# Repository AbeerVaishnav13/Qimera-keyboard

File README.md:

# Qimera Keyboard
Design files, 3D models, and ZMK firmware for the Qimera Keyboard

## Some pics of my build!

## Components for the Build
For this section, I will assume that you already have the basic soldering station setup with you. If not, please look into getting a good soldering iron, solder wire (lead free if possible), fume extractor, soldering flux, solder wick and/or desoldering pump (to fix any mistakes made while soldering).

- PCB: I designed a custom reversible PCB for this keyboard. There are a few options for you to get access to the design files:
    - I ordered my PCBs from OSH Park as I wanted the PCBs to have a cool look with black core and transparent solder mask (check out their '[AfterDark](https://blog.oshpark.com/2019/10/10/introducing-our-after-dark-black-fr-4-service/)' service) so that the copper layers which contain the wiring and art are visible. You can order directly from my [shared project](https://oshpark.com/shared_projects/fcaigPYl) on the OSH Park website.
    - If you want to use a different vendor, you can find the zipped Gerber files in the `pcbs` folder.
    - If you know your way around designing a PCB, you can customize your the PCB on your own by opening the PCB in KiCad or any other compatible PCB design software. Please find the KiCad project files in the `pcbs` folder.

- Functional components: The following components I ordered directly from [typeractive.xyz](https://typeractive.xyz)
    - Key switches - qty. 54
        - **NOTE:** The PCB is specifically designed for Kailh Choc v1 switches. I personally used the Kailh Pro Red switches.
    - NiceNano v2 MCU - qty. 2
    - EZ solder MCU sockets - qty. 2 (one pair of sockets for each MCU)
    - Kailh low profile keycaps - qty. 54 (make sure to include at least two homing keycaps if you need them!)
    - Kailh hotswap sockets - qty. 54
    - Right angle JST 2.0 battery connector - qty. 2
    - SMD SPDT (On/Off) switch - qty. 2
    - Momentary switch for resetting the MCU - qty. 2
    - SMD diodes - qty. 54
    - Tenting feet - qty. 4
        - **NOTE:** Instead of getting these tenting feet from typeractive, I got some [magsafe iphone mounts](https://www.amazon.com/dp/B0C22V8WSF?th=1) that come with a magnetic ring that can be stuck onto the bottom of the enclosure. This gives more flexibility for keyboard mounting options. I also purchased a [magsafe puck with a 1/4 inch screw hole](https://www.amazon.com/dp/B0CQM8L1ZQ) and some [camera clamp mounts](https://www.amazon.com/dp/B0CB5JKTBH?th=1), so that I could mount it on my chair for max comfort! (see the last pic on top)
    - Battery - qty. 2
        - You can buy either of the batteries (750mAh or 110mAh one) from typeractive and they would fit well in the enclosure.
        - **NOTE:** I chose to get neither of the aforementioned batteries. I instead got [these 1800mAh ones](https://www.amazon.com/gp/product/B09726K2LC) as I wanted the battery life to be in 'years' and not weeks :P

- Keyboard Enclosure:
    - For this build, I chose to go with a easy to assemble laset cut enclosure ordered from [SendCutSend](https://sendcutsend.com).
    - You can find three design files in the `cases` folder:
        - **Top plate**(`cases/Qimera top plate.dxf`): I recommend to get this made in 0.8mm - 1.2mm thick mild steel. The thickness of this plate is CRITICAL, because if the plate is thicker, the Kailh Choc switches won't snap into the top plate. You can choose a particular finish for it too. I went with 'Black Zinc' coating to make it look a bit nicer! :)
        - **Battery plate**(`cases/Qimera battery plate.dxf`): I got this made in 4.5mm thick transparent acrylic material so that the keyboard has a see-through back for the PCB art to be visible.
        - **Bottom plate**(`cases/Qimera bot plate.dxf`): I got this made in 3mm thick transparent acrylic material so that the keyboard has a see-through back for the PCB art to be visible.

- Travel Case:
    - You can find the travel case in `cases/Qimera travel case.stl` and it can be printed using any conventional 3D printer.
    - The travel case is designed to have some loops on the sides, through which you can pass a velcro strap to secure the two halves of the keyboard together and ensure that they don't fall out!

# Important things to keep in mind
## READ THESE VERY CAREFULLY BEFORE STARTING WITH THE BUILD!!!
- The PCB is reversible and needs some extra caution while soldering items:
    - **For diodes, power switch, and reset switch:**
        - Please make sure that all these are soldered on the SAME side of the PCB. This side will now be defined as the **BOTTOM side of each PCB** from here on. If soldered on the top side, there is a chance that the enclosure top plate wouldn't sit properly in between the PCB and the switches.
        - Also, ensure that the diodes are lined correctly while soldering them, i.e. the line on the diode matches the line on the silkscreen on which you are soldering the diode.

    - **For the MCU:**
        - The MCU needs to go "Face Up" (i.e. the side with the microchips on MCU should face up on the keyboard, see the pictures above for reference.)
        - If you think you're ready to solder the MCU now, **STOP!!**
        - Since the MCU footprint is made to be reversible, the actual row and column connections of the keyboard are connected to the line of vias on the inner side of the MCU and not where the actual MCU pins get soldered.
        - Therefore, to actually make the connections, there is a set of jumpers connected to each pin of the MCU (see the structures in the image below marked in RED.)
        - ALL OF these jumpers need to be connected on the **TOP side of each PCB** with a dab of excess solder bridging the two metal parts in gold color.
            - **WARNING!!:** This is the most CRUCIAL step and you need to BE CAREFUL while soldering the jumper as just a little accidental flick of the soldering iron or a bit of excess solder could lead to the solder overflowing into the MCU pin hole on the side, which would make things difficult while soldering the MCU socket later on.
            - **NOTE:** here the **TOP side** refers to the side of the PCB which is opposite to the side having the diodes, power switch and reset switch soldered.
        - After this tedious and important step, begin socketing the MCU by first soldering the socket in place, then placing the mill-max pins, and then placing the MCU on top and soldering it into the socket.
        - Make sure that the MCU is removable from the socket, and then re-attach it by pressing it in firmly.

    - **For the JST 2.0 battery connector:**
        - Make sure to connect the battery connector on the bottom side of the respective PCBs (same side as the diodes, power switch, and reset switch)
        - After soldering the battery connector, you will notice jumpers similar to ones near MCU. These are to ensure that the battery is connected to correct polarity when you flip one of the PCBs to use it for the other half of the keyboard.
        - Do a similar thing for connecting the jumpers near the battery connector, but this time the jumpers should be briged on the **BOTTOM side of each PCB** (the BOTTOM side being the same side with diodes, power and reset switch).

# Building and flashing ZMK firmware
For ease of use, I'm also including my ZMK config. Since, I keep changing my personal config too often, I would recommend to click on the `zmk-config-qimera` submodule and fork that repo to make your own copy of the config.

- You can now either directly edit the config and GitHub actions will build the firmware for your config, or you can use a keymap editor tool like [this](https://nickcoutsos.github.io/keymap-editor/) and connect it with your forked repo to change the keymap. Once the firmware is built, it should show up in the `Actions` tab of the repo and you can download it from there.
- Connect the left half of the keyboard to you computer via a USB-C cable, double press the reset button to put NiceNano MCU into bootloader mode, and then drag and drop the compiled UF2 firmware for the left half of the keyboard.
- Do the same with the right half.
- After powering up the keyboard for the first time, click the reset button on both halves simultaneously, and they should get paired to each other.
- Then you can proceed to pair the keyboard through bluetooth, to whatever device you like!

# Enjoy typing on and customizing your new Qimera Keyboard! :D

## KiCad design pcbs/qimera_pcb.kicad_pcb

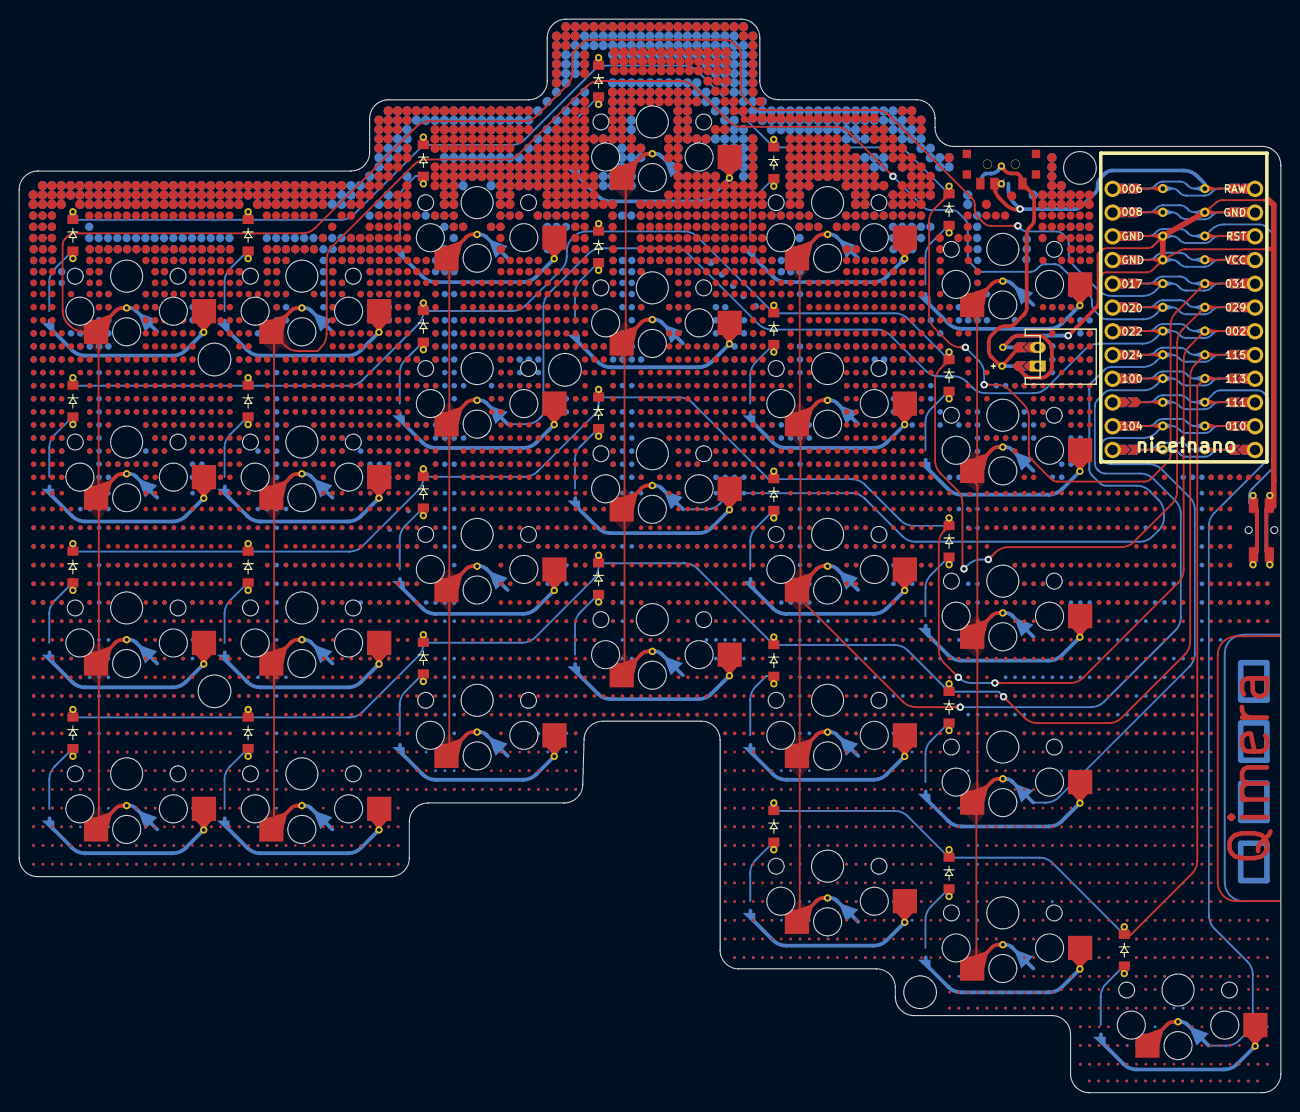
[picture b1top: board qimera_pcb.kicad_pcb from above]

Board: 2 copper layers, 135.0 x 114.9 mm, 58 parts (0 on the bottom side), 14 nets.

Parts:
B1: Momentary_reset_switch
D27, D27#2, D27#3, D27#4, D27#5, D27#6, D28, D29, D30, D31, D32, D33, D34, D35, D36, D37, D38, D39, D40, D41, D42, D42#2, D42#3, D43, D43#2, D44, D45: SMTDiode
JST1: Val**; JST_PH_S2B-PH-K_02x2.00mm_Angled_custom
MCU1: nice_nano_v2_reversible
S5, S6, S7, S8, S9, S10, S11, S12, S13, S14, S15, S16, S17, S18, S19, S20, S21, S22, S23, S24, S25, S26, S27, S28, S29, S30, S31: Kailh Choc 1u
T1: SPDT_power_switch

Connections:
GND: B1.1, B1.5, JST1.4, MCU1.3, MCU1.6, MCU1.8
RAW: MCU1.1, T1.2
RST: B1.2, MCU1.5
VBATT: JST1.3, T1.1
col1: MCU1.10, S5.1
col2: MCU1.12, S6.1
col3: MCU1.14, S7.1
col4: MCU1.16, S8.1
col5: MCU1.18, S9.1, S21.1
row1: D27#5.1, MCU1.9
row2: D30.1, MCU1.11
row3: D36.1, MCU1.13
row4: D42#3.1, MCU1.15
row5: D42#2.1, MCU1.17

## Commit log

2024-11-03 Add all the parts for the keyboard build
2024-11-05 Added images and added build instructions to README
2024-11-05 Replace heic images with png and fix errors in readme
2024-11-05 Spell check and added a link
2024-11-05 Fix grammar
